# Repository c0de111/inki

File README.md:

# Tinta

Tinta is a battery-powered ePaper sign built around the Raspberry Pi Pico W. A real-time clock
wakes it on schedule, it fetches data over Wi-Fi, redraws the screen, and then switches itself off
completely in hardware — there is no sleep mode. A push button or an NFC tap wakes it on demand.
This approach earned an Honorable Mention in the "Least Power" category of
[Hackaday's 2026 Green-Powered Challenge](https://hackaday.com/2026/05/07/congratulations-to-the-green-powered-challenge-winners/).
One set of ordinary alkaline cells lasts thousands of refresh cycles, and the ePaper keeps its
image while the device is off.

This repository holds everything needed to build one: firmware, PCB design, 3D-printable enclosure,
and an optional telemetry service. Formerly published as **inki**.

[Crowd Supply campaign](https://www.crowdsupply.com/wake-electronics/tinta) · [Hackaday logs](https://hackaday.io/project/203726-tinta-low-power-wireless-epaper-device) · [Mastodon](https://hachyderm.io/@tinta) · [MakerTube](https://makertube.net/c/tinta) · [YouTube](https://www.youtube.com/@tinta-gadget)

<p align="center">
  
</p>

---

## Try it on a bare Pico W

No custom hardware required — the firmware runs on a stock Pico W with the display disabled.

1. Download a prebuilt UF2 from the [latest release](https://github.com/c0de111/tinta/releases/latest):
   [seatsurfing](https://github.com/c0de111/tinta/releases/latest/download/inki_seatsurfing.uf2) ·
   [historian](https://github.com/c0de111/tinta/releases/latest/download/inki_historian.uf2) ·
   [homematic](https://github.com/c0de111/tinta/releases/latest/download/inki_homematic.uf2)
2. Hold BOOTSEL while plugging in the Pico W, then copy the UF2 to the `RPI-RP2` drive.
3. The onboard LED blinks `inki` in Morse once it is up.
4. Connect to the Wi-Fi access point `inki-setup` and open `http://192.168.4.1`.

> Release artifacts and the setup access point still carry the old `inki` name.

## Build from source

Building, flashing, use-case selection, and the debug output are documented in
**[firmware/README.md](firmware/README.md)**. In short:

```
cd firmware/c
./build.sh --seatsurfing        # or --historian, --homematic, --weathermap
```

Requires the Pico SDK 2.1.0 (`PICO_SDK_PATH`), the ARM GNU toolchain, and CMake 3.12+.
The build produces a bootloader, two firmware slots for over-the-air updates, and a default
configuration image.

## Repository layout

```
firmware/       Pico W firmware in C — build system, use cases, drivers, web interface
hardware/       KiCad schematic and PCB (circuit/), FreeCAD and STL enclosure (enclosure/)
inki-monitor/   optional Python/Flask service collecting battery and Wi-Fi telemetry
scripts/        helper scripts
images/         photographs and diagrams used in the documentation
```

Each directory has its own README with the details.

## Hardware

The [enclosure](hardware/enclosure/) is modular and 3D-printable, with a dovetail mount: the
baseplate is glued or screwed to the wall and the sign clips on, so it lifts straight off for a
battery change.

The [circuit](hardware/circuit/) is a custom PCB carrying the Pico W, a real-time clock, MOSFET
power switching, battery monitoring, and an optional NFC front end.

## NFC

Boards with the optional ST25DV04KC tag can be reached by a phone **while the device is switched
off**: the phone's field powers the tag, the phone writes a short command into its EEPROM, and the
tag pulls the wake line. The Pico W then boots, reads the command over I²C, and acts on it — so a
tap can refresh the display or book a desk without the device having been powered at all.

The 16-byte wire format, the wake-source decision tree, and the antenna tuning helper are described
in [firmware/README.md](firmware/README.md) and [firmware/c/README.md](firmware/c/README.md). The
companion Android app lives in its own repository,
[wake-electronics/tinta-tap](https://github.com/wake-electronics/tinta-tap).

## Field results

A 4.2-inch unit running the Seatsurfing use case has been logged continuously in an office:

```
393 days, 5142 wake cycles on one set of three AAA cells
99.5 % day coverage; one outage in 393 days (66.6 h, external cause)
45-minute wake interval, median 2700.0 s over 13 months, no measurable drift
```

The 4.2-inch version is rated at about 5,000 wake cycles on three AAA cells, the 7.5-inch version
at about 10,000 on three AA cells. The unit above met that rating in the field and kept going.
Actual runtime follows the configured wake interval: a longer interval means fewer cycles per day
and a longer life on the same cells.

## License

This project contains both hardware and software components, licensed under separate terms:

- Everything in **/hardware** is licensed under the
  **CERN Open Hardware License v2 — Strongly Reciprocal (CERN-OHL-S-2.0)**.
- All original content in **/firmware** is licensed under the **Apache License, Version 2.0**.
  Bundled third-party components under `/firmware/c/third_party/` retain their upstream licenses —
  see [firmware/c/third_party/README.md](firmware/c/third_party/README.md).

See the LICENSE files in the respective directories for the full texts.

## Contributing

Issues and pull requests are welcome, particularly new use cases: one directory under
`firmware/c/` and one build flag, see [firmware/README.md](firmware/README.md).

Contact: [c0de@posteo.de](mailto:c0de@posteo.de)

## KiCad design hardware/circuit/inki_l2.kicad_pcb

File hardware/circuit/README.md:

# Tinta Circuit

This directory contains the schematic and hardware documentation for the **Tinta** PCB. There is also a former hand-solderable design, see [`legacy/`](legacy/).

---

## Overview

The Tinta circuit is designed for long-term operation (years) using 3×AAA or 3×AA
batteries. It uses a real-time clock for accurate timekeeping and wake-up scheduling —
either a DS3231 or RV-3028, detected automatically at runtime — combined with
MOSFET-based power switching to fully disconnect the controller between wake cycles.
During wake cycles, information is fetched via Wi-Fi and displayed on an ePaper display
that retains its content without power.

Key features:
- **MOSFET power switching** — Pico W fully disconnected during sleep, drawing only µA from the RTC and passives
- **Dual RTC support** — DS3231 or RV-3028, auto-detected at runtime via I2C
- **NFC wake and control** — ST25 chip powered by RF field when Pico is off
- **Board identity straps** — 4-bit hardware profile (GP0–GP3) selects display type and hardware variant at boot
- **Push button inputs** — manual wake, page selection, and on-demand fetches

---

## Concept, Functional Blocks and Components

The power control concept works as follows: in the default (sleep) state **Q1** is off
and the Pico W has no supply voltage. Three sources can wake the system: an RTC alarm
(DS3231 or RV-3028 via their INT pin), a **pushbutton**, or an NFC field event from the
ST25DV. Once Q1 switches on, the Pico pulls down the gate of **Q2**
to hold power, executes its program, sets the next RTC alarm, and cuts power by releasing
Q1 — returning to the µA idle state.

The ePaper display is controlled via SPI; RTC and NFC communicate via I2C.

Manual user interaction:
- **Pushbuttons #0–3**: on current boards the buttons are diode-OR'd into the wake line,
  so **any of the four wakes the device**. On earlier boards only #0 wakes it.
- **Pushbuttons #1–3**: also read once at startup to select the page — hold them while the
  device powers on. Page selection works the same on both board generations.
- **ST25 NFC**: write an NFC message to the tag to trigger a wake or page selection

<table>
<tr>
  <td style="padding: 20px;"></td>
  <td style="padding: 20px;"></td>
</tr>
<tr>
  <td align="center" style="padding: 20px;"><em>Tinta board – for details use KiCAD</em></td>
  <td align="center" style="padding: 20px;"><em>schematic – <a href="inki_l2.pdf">PDF</a> · for details use KiCAD</em></td>
</tr>
</table>

---

## Board Identity Straps (R8–R11)

Four 10k pull-up resistors on GP0–GP3 encode the board profile as a 4-bit code read at
boot to determine display type and hardware configuration.

- **Populated resistor** = bit reads `1`
- **Empty pad** = bit reads `0` (firmware applies internal pull-down)

| Code | R8  | R9  | R10 | R11 | Display | Coin Cell | Board                     |
|------|-----|-----|-----|-----|---------|-----------|---------------------------|
| 0x00 | —   | —   | —   | —   | ?       | yes       | Legacy / unstrapped       |
| 0x01 | 10k | —   | —   | —   | 7.5"    | yes       | L1, 7.5"                  |
| 0x02 | —   | 10k | —   | —   | 4.2"    | yes       | L1, 4.2"                  |
| 0x03 | 10k | 10k | —   | —   | 7.5"    | yes       | L2, 7.5"                  |
| 0x04 | —   | —   | 10k | —   | 4.2"    | yes       | L2, 4.2"                  |
| 0x05 | 10k | —   | 10k | —   | 7.5"    | no        | L2 minimal (no coin cell) |
| 0x06 | —   | 10k | 10k | —   | 4.2"    | no        | L2 minimal 4.2" (no coin cell) |
| 0x07–0x0F | — | — | — | — | —      | —         | (reserved)                |

I2C devices (RTC, NFC) are auto-detected via bus scan — not encoded in straps. Buttons
and LED do not require strap encoding.

---

## RTC Backend Selection

The firmware auto-detects the RTC at runtime via I2C bus scan:
- **DS3231** at 0x68 — classic, high-accuracy, moderate power (~200 µA active)
- **RV-3028** at 0x52 — ultra-low power (~45 nA idle), AMBA/Micro Crystal

Both provide alarm-based wake scheduling. The RV-3028 improves idle power budget
significantly for high-frequency refresh use cases.

---

## NFC Integration (ST25DV04KC)

The ST25DV NFC tag is powered from the RF field when the Pico is off (0 mA from battery).
Its GPIO-controlled VCC line (GP18) is held low during sleep. An NFC write from a phone
or reader pulls the ST25 INT line, which feeds into the wake circuit — waking the device
without a button press. The firmware reads the NFC payload at startup to determine the
requested page or action.

---

## Power Consumption and Estimations

Typical battery life can be estimated with
[`power_consumption_estimate.py`](power_consumption_estimate.py). Edit the parameters at the top
of the script and run it; the two examples below are its output.

### Power Consumption Estimate for 4.2"

Parameters taken from a real deployment — the field unit whose discharge curve is shown below.

**Used Parameters**

- **Idle current**: 5 µA (RTC consumption, residual current via pullups and others)
- **Activation consumption**: 0.250 mAh per wake-up (same for 4.2" and 7.5", measured — the
  ePaper refresh is not a significant contribution)
- **LED consumption** (included above): 0.021 mAh per wake-up
- **Wake-up schedule**: 18.3× per day, 5 days per week
- **Battery self-discharge**: 2.5 % per year
- **Battery capacity**: 1200 mAh (AAA batteries)

**Annualized Consumption Rates (approximate)**

- **Idle**: 43.8 mAh/year
- **Active (wake-ups)**: 1192.8 mAh/year

**⇒ Estimated battery lifetime: 350 days (≈ 0.96 years)**

**Yearly Breakdown**

| Year | Self-Discharge (mAh) | Fixed Consumption (mAh) |
|------|----------------------|--------------------------|
| 1    | 14.32                | 1185.75                  |

<p align="center">
  
</p>

<p align="center"><i>The same unit, measured: 393 days and 5142 wake cycles on one set of AAA
cells, logged at every wake. The scheduled interval held a median of exactly 2700.0 s, in each of
the 13 months, with a p95 jitter of about 7 s that did not change as the pack drained; the
discharge fits a straight line at R² = 0.987. One interruption occurred in the whole period,
66 hours in January 2026, appearing at the same time in the logs of five other units on the same
server.</i></p>

---

### Power Consumption Estimate for 7.5"

**Used Parameters**

- **Idle current**: 5 µA (RTC consumption, residual current via pullups and others)
- **Activation consumption**: 0.250 mAh per wake-up (same for 4.2" and 7.5", measured — the
  ePaper refresh is not a significant contribution)
- **LED consumption** (included above): 0.021 mAh per wake-up
- **Wake-up schedule**: 12× per day, 5 days per week
- **Battery self-discharge**: 2.5 % per year
- **Battery capacity**: 2500 mAh (AA batteries)

**Annualized Consumption Rates (approximate)**

- **Idle**: 43.8 mAh/year
- **Active (wake-ups)**: 782.1 mAh/year

**⇒ Estimated battery lifetime: 1065 days (≈ 2.92 years)**

**Yearly Breakdown**

| Year | Self-Discharge (mAh) | Fixed Consumption (mAh) |
|------|----------------------|--------------------------|
| 1    | 51.48                | 826.80                   |
| 2    | 29.82                | 826.80                   |
| 3    | 8.76                 | 757.20                   |

---

## RTC Backup Supply

Some boards carry a coin cell (**BT1**, e.g. CR1225) feeding the RTC's VBAT pin through a
diode-OR (**D1**, **D2**) alongside the main battery. It is optional and no longer fitted:
Tinta re-syncs the RTC from the network at every wake cycle, so the RTC only has to hold time
between cycles, which the main cells do. The board identity straps record which variant a given
board is.

---

## Key Components

- **Q1**: P-channel MOSFET — main power switch, disconnects Pico during sleep
- **Q2**: N-channel MOSFET — power latch (Pico holds itself on)
- **U1**: Raspberry Pi Pico W — main controller (Wi-Fi, ePaper, I2C, SPI)
- **U2**: DS3231SN or RV-3028 — RTC, alarm wake, I2C (auto-detected)
- **U3**: ST25DV04KC — NFC tag, ISO 15693, I2C, RF-powered when Pico off
- **R8–R11**: Board identity straps (10k pull-ups on GP0–GP3)
- **D1/D2, BT1**: optional diode-OR and coin cell for RTC backup (not fitted on current boards)

---

## Files

- `inki_l2.pdf` — schematic PDF (no KiCad required)
- `inki_l2.kicad_sch` — main schematic
- `inki_l2.kicad_pcb` — PCB layout
- `inki_l2_BOM.csv` — bill of materials
- `wake_sources.kicad_sch` — wake circuit sub-schematic
- `optional_i2c_device.kicad_sch` — optional I2C device sub-schematic
- `power_consumption_estimate.py` — battery lifetime model (edit parameters, run)
- `project-libraries/` — custom KiCad symbols and footprints

---

## Legacy Design

A former hand-solderable design is preserved in [`legacy/`](legacy/). It supports DS3231
only and has no NFC or identity straps, but can be assembled by an experienced solderer
without SMD equipment.

---

## License

This hardware is published under the **CERN-OHL-S v2** license.

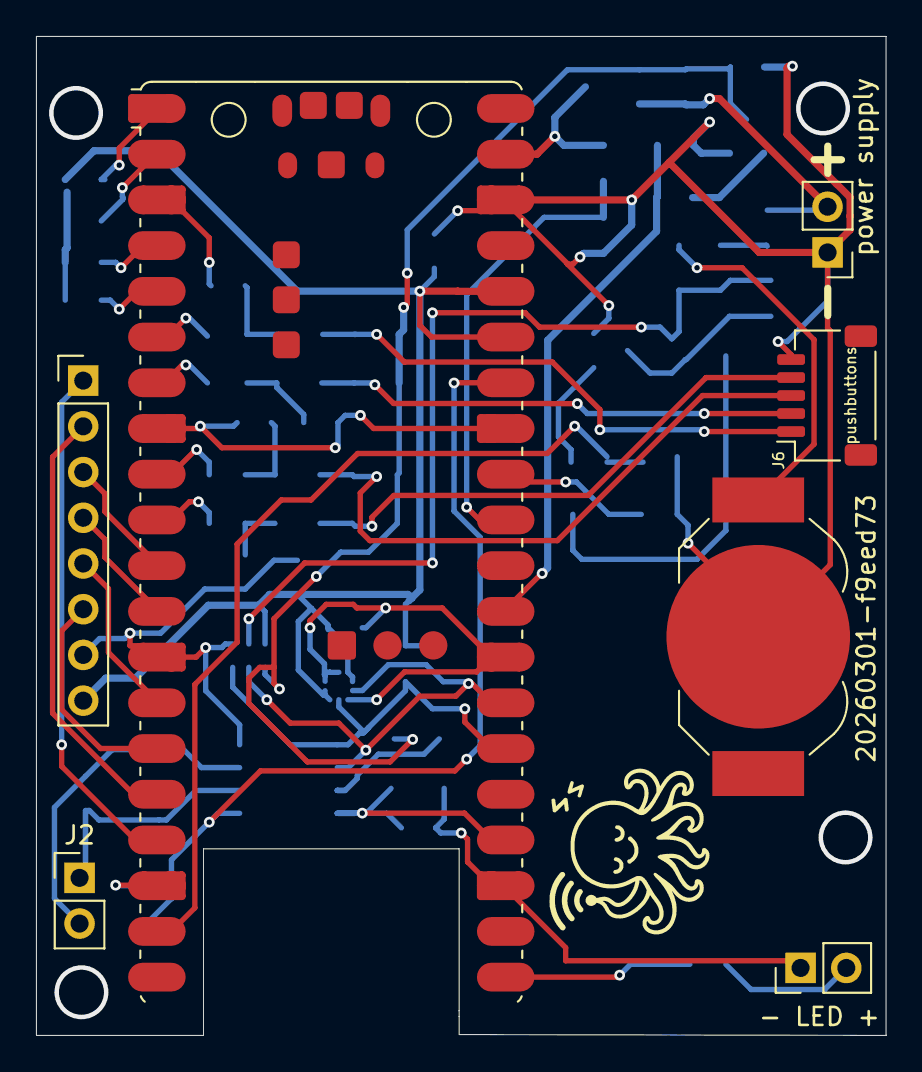
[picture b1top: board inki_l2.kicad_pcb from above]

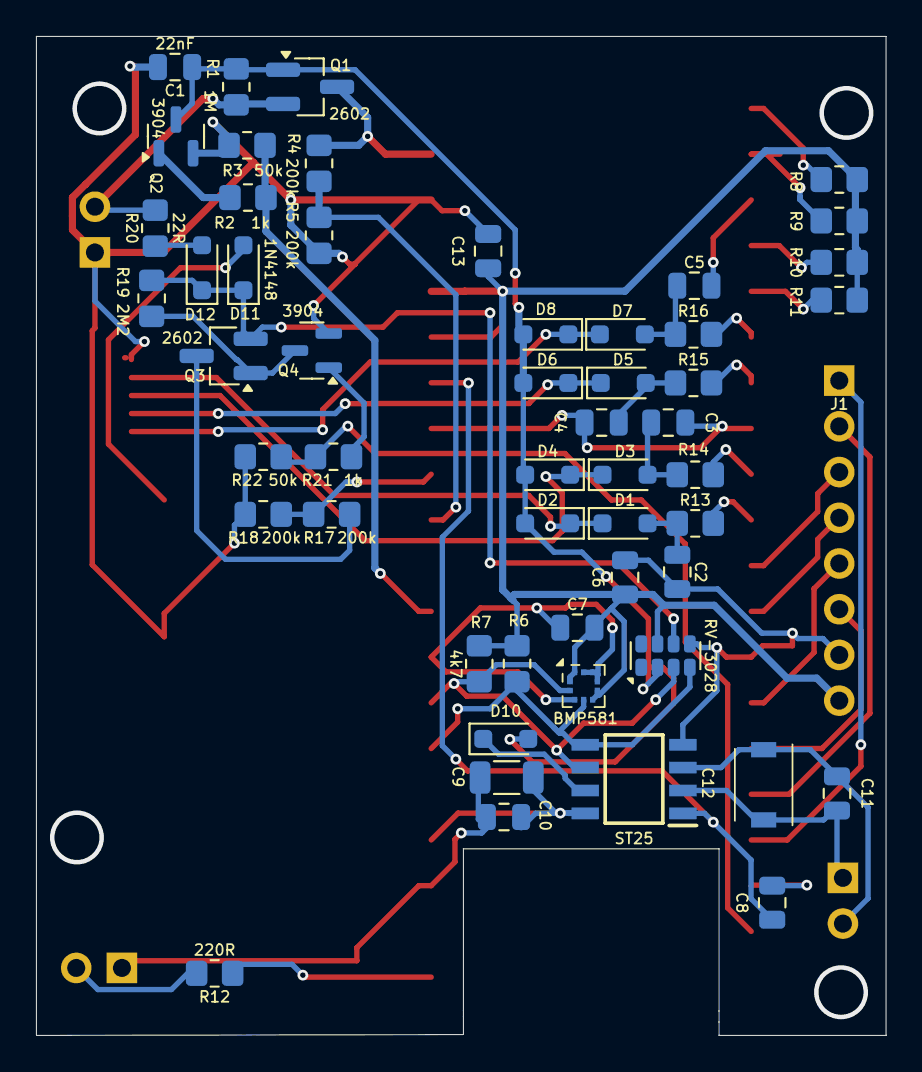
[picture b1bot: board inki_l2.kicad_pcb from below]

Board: 2 copper layers, 47.2 x 55.5 mm, 60 parts (53 on the bottom side), 47 nets.

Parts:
BT1: Coin Cell (RTC Backup); BatteryHolder_LINX_BAT-HLD-012-SMT
C1: 22nF; C_0805_2012Metric
C2, C3, C4, C5, C6, C7, C8, C10, C13: 100nF; C_0805_2012Metric
C9: 4.7uF; C_1206_3216Metric
C11: 10pF; C_0805_2012Metric
C12: JZ400
D1, D2, D3, D4, D5, D6, D7, D8, D10, D11: BAT54J; D_SOD-323_HandSoldering
D12: 1N4148; D_SOD-323_HandSoldering
J1: connector epaper; PinHeader_1x08_P2.54mm_Vertical
J2: antenna; PinHeader_1x02_P2.54mm_Vertical
J3: Battery 3xAA/AAA; PinHeader_1x02_P2.54mm_Vertical
J6: pushbuttons; JST_SH_SM05B-SRSS-TB_1x05-1MP_P1.00mm_Horizontal
J7: status LED; PinHeader_1x02_P2.54mm_Vertical
Q1, Q3: 2602; SOT-23_Handsoldering
Q2, Q4: 3904; SOT-23
R1: 1M; R_0805_2012Metric_Pad1.20x1.40mm_HandSolder
R2, R13, R14, R15, R16, R21: 1k; R_0805_2012Metric_Pad1.20x1.40mm_HandSolder
R3, R22: 50k; R_0805_2012Metric_Pad1.20x1.40mm_HandSolder
R4, R5, R17, R18: 200k; R_0805_2012Metric_Pad1.20x1.40mm_HandSolder
R6, R7: 4k7; R_0805_2012Metric_Pad1.20x1.40mm_HandSolder
R8, R9, R10, R11: 10k; R_0805_2012Metric_Pad1.20x1.40mm_HandSolder
R12: 220R; R_0805_2012Metric_Pad1.20x1.40mm_HandSolder
R19: 2M2; R_0805_2012Metric_Pad1.20x1.40mm_HandSolder
R20: 22R; R_0805_2012Metric_Pad1.20x1.40mm_HandSolder
U2: BMP581
U4: RV-3028; MicroCrystal_C7_SON-8_1.5x3.2mm_P0.9mm
U5: ST25; SOIC127P600X175-8N
pico1: SC0918; RaspberryPi_Pico_W_SMD

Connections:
3V3: C6.1, C7.1, C13.1, J1.8, R6.1, R7.1, R8.1, R9.1, R10.1, R11.1, U2.1 (VDDIO), U2.5 (SDO), U2.6 (CSB), U2.10 (VDD), U4.7 (VDD), pico1.35 (ADC_VREF), pico1.36 (3V3_OUT)
/BUSY: J1.1, pico1.17 (GP13)
/CLK: J1.5, pico1.14 (GP10)
/CS: J1.4, pico1.12 (GP9)
/DC: J1.3, pico1.11 (GP8)
/DIN: J1.6, pico1.15 (GP11)
/RST: J1.2, pico1.16 (GP12)
ADC_RTC_VBAT: R17.2, R18.1, pico1.32 (GP27)
BAT_RAW: J3.2, Q1.2 (S), R1.1, R20.2
GND: BT1.2 (-), C1.2, C2.2, C3.2, C4.2, C5.2, C6.2, C7.2, C8.2, C9.2, C10.2, C13.2, J1.7, J3.1, J6.5, J7.1, Q2.2 (E), Q4.2 (E), R3.2, R5.2, R18.2, R22.1, U2.3 (VSS), U2.7 (INT), U2.8 (VSS), U2.9 (VSS), U4.5 (VSS), U5.4 (VSS), pico1.3 (GND), pico1.8 (GND), pico1.13 (GND), pico1.18 (GND), pico1.23 (GND), pico1.28 (GND), pico1.33 (AGND), pico1.38 (GND)
unnamed: BT1.1 (+), D11.2 (A)
unnamed: C2.1, D1.2 (A), R13.1
unnamed: D1.1 (K), D2.1 (K), J6.4
unnamed: C3.1, D3.2 (A), R14.1
unnamed: D3.1 (K), D4.1 (K), J6.3
unnamed: C4.1, D5.2 (A), R15.1
unnamed: D5.1 (K), D6.1 (K), J6.2
unnamed: C5.1, D7.2 (A), R16.1
unnamed: D7.1 (K), D8.1 (K), J6.1
unnamed: D10.1 (K), U5.7 (GPO_(OPEN_DRAIN))
unnamed: D12.2 (A), R20.1
unnamed: C11.2, C12.2, J2.1, U5.2 (AC0)
unnamed: C11.1, C12.1, J2.2, U5.3 (AC1)
unnamed: J7.2, R12.2
unnamed: Q1.3 (D), R4.2, pico1.39 (VSYS)
unnamed: Q2.1 (B), R2.1
unnamed: Q3.3 (D), R17.1
unnamed: Q3.1 (G), Q4.3 (C), R19.2
unnamed: Q4.1 (B), R21.2
unnamed: R8.2, pico1.1 (GP0)
unnamed: R9.2, pico1.2 (GP1)
unnamed: R10.2, pico1.4 (GP2)
unnamed: R11.2, pico1.5 (GP3)
unnamed: R21.1, R22.2, pico1.19 (GP14)
unnamed: R12.1, pico1.21 (GP16)
unnamed: R2.2, R3.1, pico1.29 (GP22)
unnamed: R4.1, R5.1, pico1.31 (GP26)
PB1_GPIO: R13.2, pico1.10 (GP7)
PB2_GPIO: R14.2, pico1.9 (GP6)
PB3_GPIO: R15.2, pico1.7 (GP5)
PB4_GPIO: R16.2, pico1.6 (GP4)
RTC_VBAT: D11.1 (K), D12.1 (K), Q3.2 (S), R19.1, U4.6 (VBACKUP)
SCL: R7.2, U2.2 (SCK), U4.3 (SCL), U5.6 (SCL), pico1.27 (GP21)
SDA: R6.2, U2.4 (SDI), U4.4 (SDA), U5.5 (SDA), pico1.26 (GP20)
VCC_ST25: C9.1, C10.1, U5.8 (VCC), pico1.24 (GP18)
V_EH_ST25: C8.1, U5.1 (V_EH), pico1.34 (GP28)
WAKE: C1.1, D2.2 (A), D4.2 (A), D6.2 (A), D8.2 (A), D10.2 (A), Q1.1 (G), Q2.3 (C), R1.2, U4.2 (~INT)

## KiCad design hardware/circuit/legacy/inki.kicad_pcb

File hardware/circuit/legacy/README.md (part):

# inki Circuit

This repository contains the electronic schematic and hardware documentation for the **inki** project — a battery-powered, low-power circuit employing  a Raspberry Pi Pico W and a DS3231 RTC module for wireless ePaper display - as for instance for room signage.

---

## Overview
The inki circuit is designed for long-term operation (years) using 3×AAA or 3×AA batteries. It uses a DS3231 real-time clock for accurate timekeeping and wake-up scheduling, combined with MOSFET-based power switching to fully disconnect the controller to minimize power consumption between wake cycles. During wake cycles information is fetched via WIFI and displayed on an epaper which retains its display without power consumption.

---

## Concept, Functional Blocks and Components

In the default state of the circuit, **Q1** is in the off-state and the Pico does not get any supply voltage. Two events can switch **Q1** on via its gate and thus power the Pico: An alarm from the RTC **DS3231** via its INT pin, or a manual trigger via **pushbutton #0**. If this happens, the Pico will start, and as a first action in its program pull down the gate from **Q2**, so that power is maintained even if the push button is released by the user. The Pico will then execute its programme and always finish the programme with setting the next alarm in the **DS3231**, and, subsequently, finally cutting itself off power by switching **Q1** off. This leaves the Pico completely unpowered and the circuit back to the default state. In the default state, the circuits draws a **few µA** only, compared to **several mA** in the usual sleep modes of the Pico. During the wake cycle, the current drawn is approximately 50 mA for about 15 seconds. The epaper is controlled via SPI, the DS3231 via I2C.

<table>
<tr>
  <td style="padding: 20px;"></td>
  <td style="padding: 20px;"></td>
</tr>
<tr>
  <td align="center" style="padding: 20px;"><em>inki board – for details use KiCAD</em></td>
  <td align="center" style="padding: 20px;"><em>schematic – for details use KiCAD</em></td>
</tr>
</table>

Manual user interaction via:

- **SW1 / DIP switch**: Allow static configuration.
	-  **"gate"**: **pushbutton #0** can be connected to gate for manual triggering
	- **"always on"**: gate of **Q1** can be permanently grounded (powering Vsys of the Pico with Vcc) for debugging
	- **"LED"**: activate status LED, signaling running Pico
	- **"Vbat"**: Connect DS3231 Vbat to Vcc via **D2** (see below)

- **Pushbuttons** (**J2**, **J4**, **J5**):
	- **pushbutton #0** / **J2**: the same line as INT# and used for manual wake-up.
	- **pushbutton #1-3**: for manual user input, debounced by 1k resistors and 100nF caps, read once at start-up by the Pico -> First push **pushbutton #1-3**, only after that start Pico by **pushbutton #0**

---

## Power Consumption and Estimations

Typical battery life can be estimated with [`power_consumption_estimate.py`](../power_consumption_estimate.py) in the parent directory, example output for the 4.2" version:

### Power Consumption Estimate for 4.2"

**Used Parameters**

- **Idle current**: 5 µA (RTC consumption, residual current via pullups and others)
- **Activation consumption**: 0.250 mAh per wake-up (same for 4.2″ and 7.5″ versions, measured)
- **LED consumption** (included above): 0.021 mAh per wake-up
- **Wake-up schedule**: 7× per day, 5 days per week
- **Battery self-discharge**: 2.5 % per year
- **Battery capacity**: 1200 mAh (AAA batteries)

**Annualized Consumption Rates (approximate)**

- **Idle**: 43.8 mAh/year
- **Active (wake-ups)**: 456.2 mAh/year

**⇒ Estimated battery lifetime: 850 days (≈ 2.33 years)**

**Yearly Breakdown**

| Year | Self-Discharge (mAh) | Fixed Consumption (mAh) |
|------|----------------------|--------------------------|
| 1    | 23.43                | 500.55                   |
| 2    | 10.50                | 500.55                   |
| 3    | 0.68                 | 164.90                   |

This is based on measurements and gives estimations useful to gauge wake-up energy relative to idle current in order to optimize runtime versus refresh cycle.

---
### Power Consumption Estimate for 7.5"

**Used Parameters**

- **Idle current**: 5 µA (RTC consumption, residual current via pullups and others)
- **Activation consumption**: 0.250 mAh per wake-up (same for 4.2″ and 7.5″ versions, measured)
- **LED consumption** (included above): 0.021 mAh per wake-up
- **Wake-up schedule**: 48× per day, 7 days per week
- **Battery self-discharge**: 2.5 % per year
- **Battery capacity**: 2500 mAh (AA batteries)

**Annualized Consumption Rates (approximate)**

- **Idle**: 43.8 mAh/year
- **Active (wake-ups)**: 4380 mAh/year

**⇒ Estimated battery lifetime: 205 days (≈ 0.56 years)**

**Yearly Breakdown**

| Year | Self-Discharge (mAh) | Fixed Consumption (mAh) |
|------|----------------------|--------------------------|
| 1    | 17.58                | 2484.6                   |

This chart shows the measured energy consumption of the 7.5" prototype.

This is based on measurements and gives estimations useful to gauge wake-up energy relative to idle current in order to optimize runtime versus refresh cycle.

---

## Diode circuit for Vbat Supply for the DS3231

The goal of this circuit (**D1** and **D2**) is to supply the DS3231 real-time clock module with power at all times—either from the main power source (e.g. 3×AA(A) batteries) or, if unavailable, from a coin cell (e.g. CR1225). The switch between sources is passive, using one diode per supply path, and aims to minimize energy loss and especially protect the coin cell from unnecessary drain.

---

### Functional Principle

The two power sources (AAA and coin cell) are each connected to the VBAT pin through a diode. The diode with the higher input voltage (minus its forward voltage drop) determines which source supplies VBAT. The other diode remains reverse-biased and blocks current.

The intention is for the coin cell to only take over once the main battery voltage is no longer sufficient—ideally right before the microcontroller stops functioning due to low voltage. The DS3231 operates correctly on VBAT voltages between 2.3 V and 6.0 V, with 3.0 V being typical for coin-cell powered backup operation.

---

### D1 = 1N4148 (standard silicon diode), D2 = BAT54 (Schottky)

| Source      | Diode   | Forward Voltage (Vf) | Notes                                        |
|-------------|---------|----------------------|-----------------------------------------------|
| AAA         | 1N4148  | ~0.7 V               | Higher voltage drop, prioritizes AAA clearly |
| Coin cell   | BAT54   | ~0.2–0.3 V           | Low drop, ideal for backup                   |

#### Advantages
- **Clear prioritization**: Coin cell only activates when AAA voltage drops below ~3.8 V.
- **Coin cell is protected** for most of the battery life.
- **Simple component selection**, widely available parts.

#### Disadvantages
- At low AAA voltages (e.g. <3.3 V), VBAT may drop below 2.6 V.
- The 1N4148 causes a non-negligible drop in VBAT during AAA operation.

#### Measurement confirming the switch behavior

An oscilloscope measurement verifies the expected behavior:

Initially (high AAA voltage), VBAT closely follows the AAA level. As the AAA voltage drops and the output of the 1N4148 falls below the coin cell’s level minus the BAT54 drop, the coin cell takes over. VBAT then stabilizes around 3.1 V and becomes independent of AAA voltage.

---

### Self-Adjusting Coin Cell Protection

As the coin cell slowly discharges over time, its output voltage decreases (e.g. from 3.3 V to 2.8 V). This naturally delays its takeover, further prioritizing the AAA battery as long as possible. This behavior provides passive and automatic coin cell protection without requiring additional logic.

#### Reverse Leakage Behavior During Passive Source Switching

During normal operation, when one source (AAA or coin cell) supplies VBAT, the unused source’s diode is reverse-biased. This raises the question of whether significant leakage current could flow back into the inactive battery, potentially causing unnecessary drain over time.

At typical room temperatures (25 °C), the expected reverse leakage currents are extremely low:

| Diode         | Typical Reverse Current @ 25 °C, ~4 V | Notes |
|---------------|----------------------------------------|-------|
| 1N4148WS      | ~1–10 nA                              | Negligible |
| BAT54 (Schottky) | ~10–100 nA                          | Higher than silicon but still negligible |

Even under worst-case assumptions (maximum datasheet values at 20–25 V reverse voltage), the leakage remains in the nanoampere range. In real-world operation at ~3–4 V reverse voltage, the leakage current is orders of magnitude smaller than the typical standby current of the DS3231 RTC itself (1.5–2.0 µA).

Thus, no practical impact on battery life is expected from reverse leakage through either diode path. The diodes reliably block the inactive source without measurable drain, maintaining the energy-saving properties of the design.

---
## A few notes about some of the components

- **Q1**: TSM260P02CX, P-channel MOSFET — disconnects the Pico W from the battery supply during sleep. Controlled via DS3231 and push button #0.
- **D1**: BAT54 Schottky diode — supplies power from the battery pack to the circuit and DS3231 VCC.
- **D2**: BAT54 Schottky diode — connects the optional coin cell to DS3231 VBAT for backup operation.
- **R1–R3**: Gate resistors for Q1 — control gate behavior during transitions, including pull-up (R2) and pull-down (R3).
- **INT#/Button**: Wake-up signal sourced from either the DS3231 alarm output or a manual pushbutton connected in parallel. The gate of Q1 is pulled low through these paths, enabling the Pico's power.
- **R7, R8**: Voltage divider for measuring the 3×AAA battery voltage. Divider is only active when **Q1** is conducting (i.e., during Pico operation).
- **U2**: DS3231SN — provides accurate timekeeping, I²C communication, and a programmable alarm interrupt controlling the whole circuit.
- **J4**: Coin cell holder — supplies VBAT to DS3231 when main power is lost.
- The DS3231 remains powered at all times to maintain time and alarm functionality.
- **Q3**: IRLML6344 N-channel MOSFET — enables a separate divider (**R1** and **R14**) to measure the voltage of the RTC coin cell (Vbat). Controlled via GP14.
- **R15**: Pull-down on Q3 gate — ensures that Q3 remains off when unpowered to eliminate leakage current.
- **GP14**: GPIO enabling VBAT divider (Q3).
- **GP27**: Analog input (ADC) for measuring voltage from the divider.

## Files and Folders

- `esign.kicad_sch`: Main schematic
- `esign.kicad_pcb`: PCB layout
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
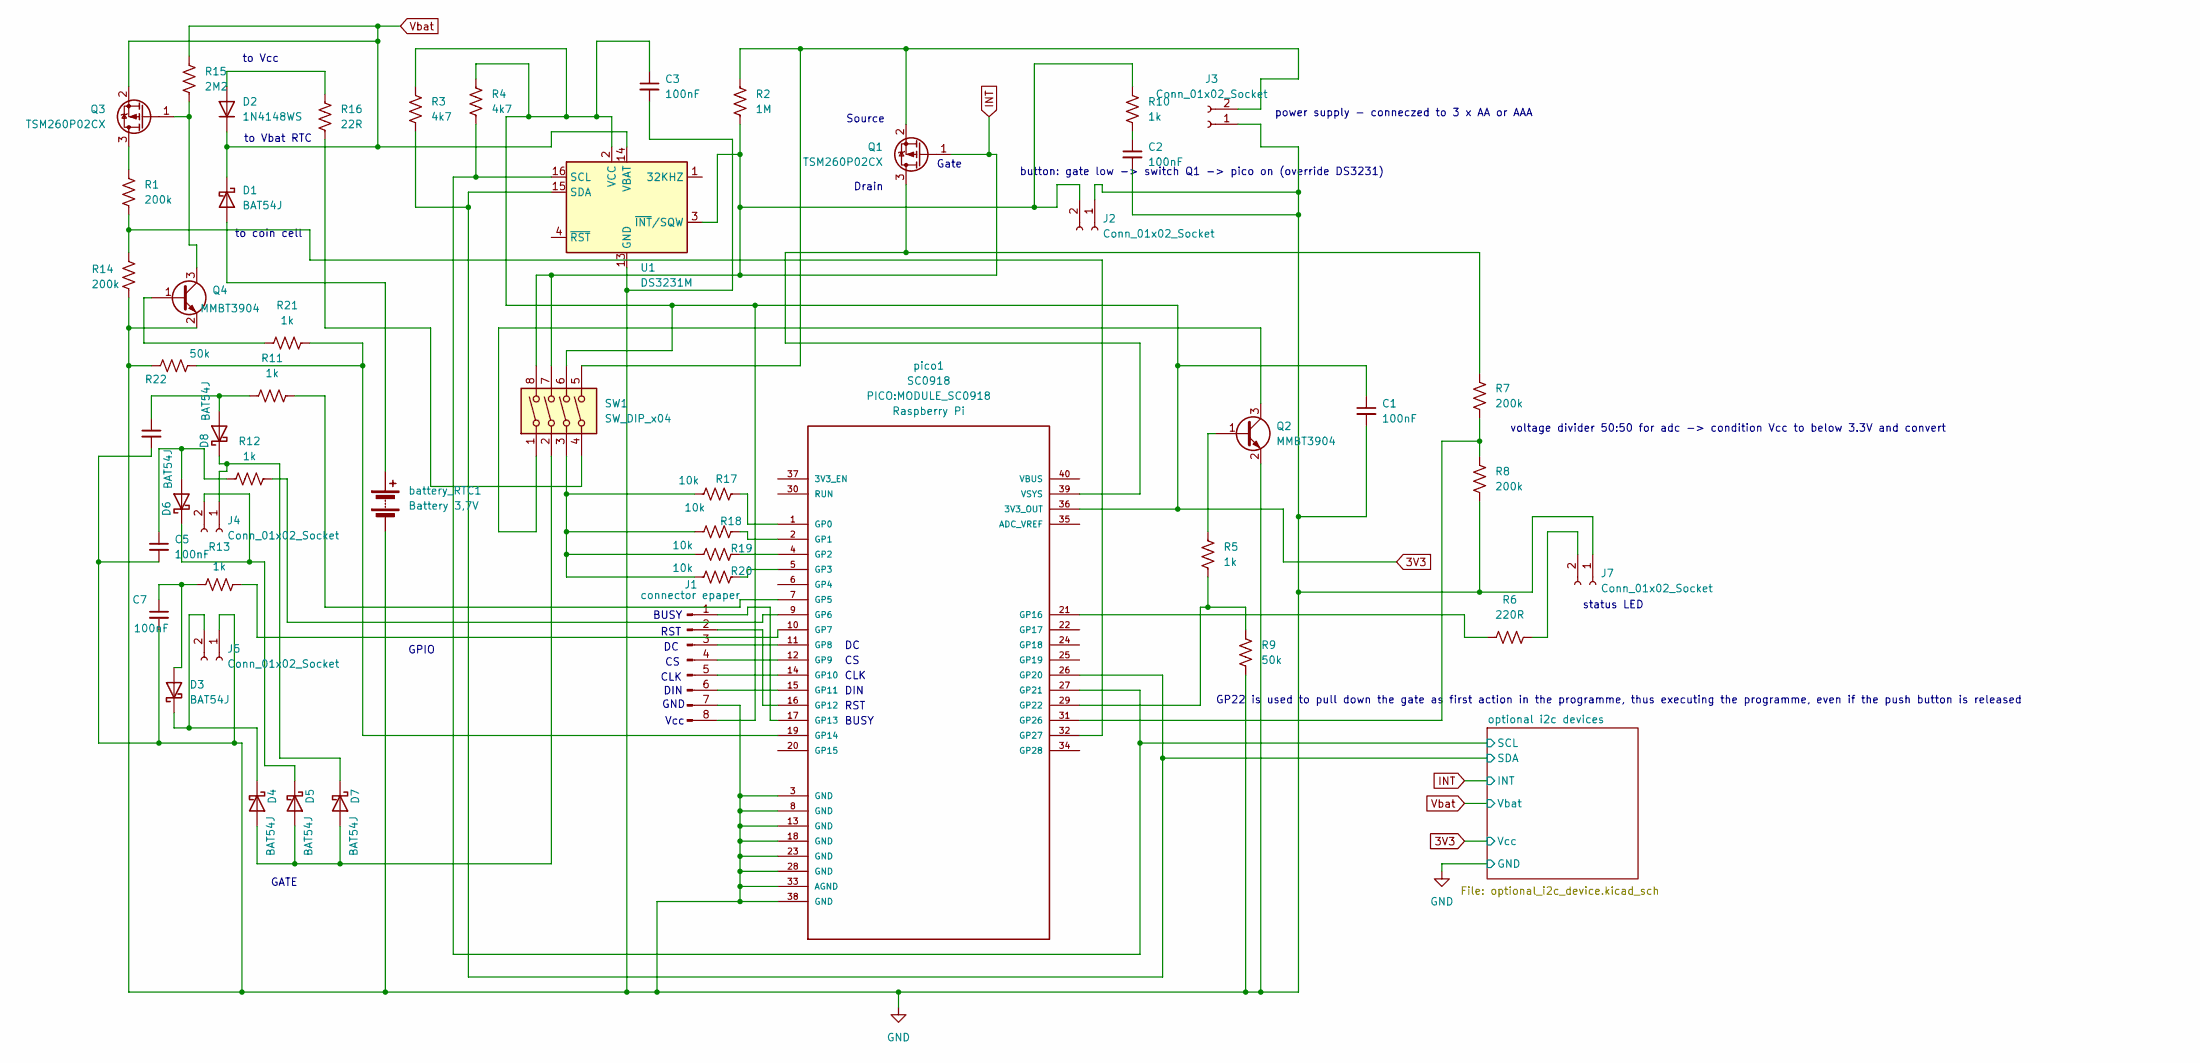
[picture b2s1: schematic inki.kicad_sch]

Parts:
C1, C2, C3, C4, C5, C7: 100nF; C_0805_2012Metric
D1, D3, D4, D5, D6, D7, D8: BAT54J; D_SOD-323_HandSoldering
D2: 1N4148WS; D_SOD-323_HandSoldering
J1: connector epaper; PinHeader_1x08_P2.54mm_Vertical
J2, J3, J4, J5, J7: Conn_01x02_Socket; PinHeader_1x02_P2.54mm_Vertical
Q1, Q3: TSM260P02CX; SOT-23_Handsoldering
Q2, Q4: MMBT3904; SOT-23
R1, R7, R8, R14: 200k; R_0805_2012Metric_Pad1.20x1.40mm_HandSolder
R2: 1M; R_0805_2012Metric_Pad1.20x1.40mm_HandSolder
R3, R4: 4k7; R_0805_2012Metric_Pad1.20x1.40mm_HandSolder
R5, R10, R11, R12, R13, R21: 1k; R_0805_2012Metric_Pad1.20x1.40mm_HandSolder
R6: 220R; R_0805_2012Metric_Pad1.20x1.40mm_HandSolder
R9, R22: 50k; R_0805_2012Metric_Pad1.20x1.40mm_HandSolder
R15: 2M2; R_0805_2012Metric_Pad1.20x1.40mm_HandSolder
R16: 22R; R_0805_2012Metric_Pad1.20x1.40mm_HandSolder
R17, R18, R19, R20: 10k; R_0805_2012Metric_Pad1.20x1.40mm_HandSolder
SW1: SW_DIP_x04; SW_DIP_SPSTx04_Slide_9.78x12.34mm_W8.61mm_P2.54mm
U1: DS3231M; SOIC-16W_7.5x10.3mm_P1.27mm
battery_RTC1: Battery 3,7V; BatteryHolder_LINX_BAT-HLD-012-SMT
pico1: SC0918; MODULE_SC0918; PARTREV 1.6

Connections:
3V3: C1.1, C3.1, J1.8, R3.1, R4.1, SW1.6, U1.2 (VCC), pico1.36 (3V3_OUT); also elsewhere on the board
/optional i2c devices/SCL: R4.2, U1.16 (SCL), pico1.27 (GP21); also elsewhere on the board
/optional i2c devices/SDA: R3.2, U1.15 (SDA), pico1.26 (GP20); also elsewhere on the board
GND: C1.2, C2.2, C3.2, C4.2, C5.2, C7.2, J1.7, J2.1, J3.1, J5.1, J7.1, Q2.2 (E), Q4.2 (E), R8.2, R9.2, R14.2, R22.1, U1.5 (GND), U1.6 (GND), U1.7 (GND), U1.8 (GND), U1.9 (GND), U1.10 (GND), U1.11 (GND), U1.12 (GND), U1.13 (GND), battery_RTC1.2 (-), pico1.3 (GND), pico1.8 (GND), pico1.13 (GND), pico1.18 (GND), pico1.23 (GND), pico1.28 (GND), pico1.33 (AGND), pico1.38 (GND); also elsewhere on the board
INT: J2.2, Q1.1 (G), R2.2, R10.2, SW1.7, SW1.8, U1.3 (~INT/SQW); also elsewhere on the board
unnamed: C2.1, R10.1
unnamed: D1.2 (A), battery_RTC1.1 (+)
unnamed: D2.2 (A), R16.1
unnamed: C7.1, D3.2 (A), R13.2
unnamed: D3.1 (K), D4.1 (K), J5.2
unnamed: D4.2 (A), D5.2 (A), D7.2 (A), SW1.2
unnamed: D5.1 (K), D6.1 (K), J4.2
unnamed: C5.1, D6.2 (A), R12.2
unnamed: D7.1 (K), D8.1 (K), J4.1
unnamed: C4.1, D8.2 (A), R11.2
unnamed: J1.1, pico1.17 (GP13)
unnamed: J1.2, pico1.16 (GP12)
unnamed: J1.3, pico1.11 (GP8)
unnamed: J1.4, pico1.12 (GP9)
unnamed: J1.5, pico1.14 (GP10)
unnamed: J1.6, pico1.15 (GP11)
unnamed: J3.2, Q1.2 (S), R2.1, SW1.5
unnamed: J7.2, R6.2
unnamed: Q1.3 (D), R7.1, pico1.39 (VSYS)
unnamed: Q2.1 (B), R5.1
unnamed: Q2.3 (C), SW1.1
unnamed: Q3.3 (D), R1.1
unnamed: Q3.1 (G), Q4.3 (C), R15.2
unnamed: Q4.1 (B), R21.2
unnamed: R16.2, SW1.4
unnamed: R17.1, R18.1, R19.1, R20.1, SW1.3
unnamed: R17.2, pico1.1 (GP0)
unnamed: R18.2, pico1.2 (GP1)
unnamed: R19.2, pico1.4 (GP2)
unnamed: R20.2, pico1.5 (GP3)
unnamed: R11.1, pico1.7 (GP5)
unnamed: R12.1, pico1.9 (GP6)
unnamed: R13.1, pico1.10 (GP7)
unnamed: R21.1, R22.2, pico1.19 (GP14)
unnamed: R6.1, pico1.21 (GP16)
unnamed: R5.2, R9.1, pico1.29 (GP22)
unnamed: R7.2, R8.1, pico1.31 (GP26)
unnamed: R1.2, R14.1, pico1.32 (GP27)
Vbat: D1.1 (K), D2.1 (K), Q3.2 (S), R15.1, U1.14 (VBAT); also elsewhere on the board

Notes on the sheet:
CLK
Vcc
to Vcc
voltage divider 50:50 for adc -> condition Vcc to below 3.3V and convert
button: gate low -> switch Q1 -> pico on (override DS3231)
to Vbat RTC
status LED
RST
GP22 is used to pull down the gate as first action in the programme, thus executing the programme, even if the push button is released
DIN
GND
BUSY
Drain
GATE
Source
GPIO
to coin cell
power supply - conneczed to 3 x AA or AAA
Gate

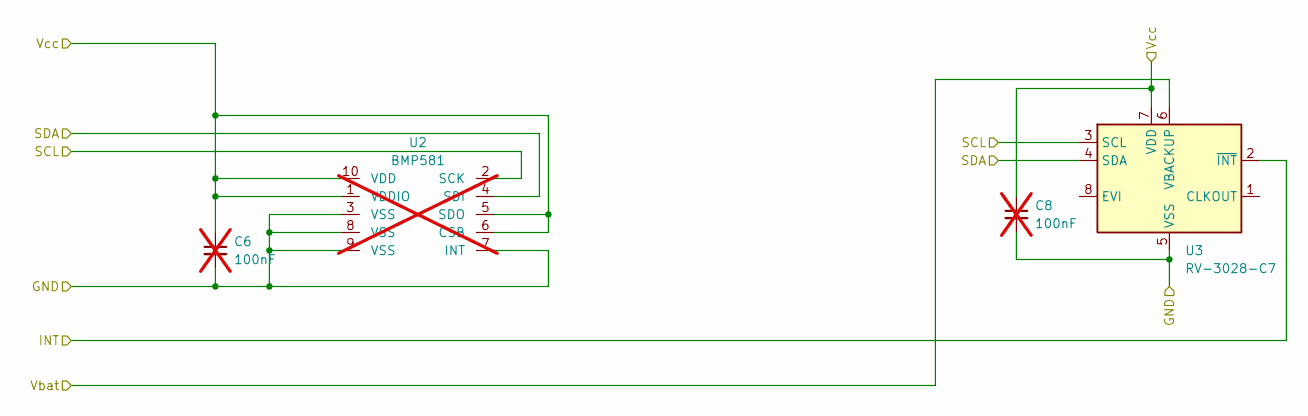
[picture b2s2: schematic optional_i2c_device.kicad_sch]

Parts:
C6, C8: 100nF; C_0805_2012Metric; not fitted
U2: BMP581; not fitted
U3: RV-3028-C7; MicroCrystal_C7_SON-8_1.5x3.2mm_P0.9mm

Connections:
3V3: C6.1, C8.1, U2.1 (VDDIO), U2.5 (SDO), U2.6 (CSB), U2.10 (VDD), U3.7 (VDD); also elsewhere on the board
/optional i2c devices/SCL: U2.2 (SCK), U3.3 (SCL); also elsewhere on the board
/optional i2c devices/SDA: U2.4 (SDI), U3.4 (SDA); also elsewhere on the board
GND: C6.2, C8.2, U2.3 (VSS), U2.7 (INT), U2.8 (VSS), U2.9 (VSS), U3.5 (VSS); also elsewhere on the board
INT: U3.2 (~INT); also elsewhere on the board
Vbat: U3.6 (VBACKUP); also elsewhere on the board

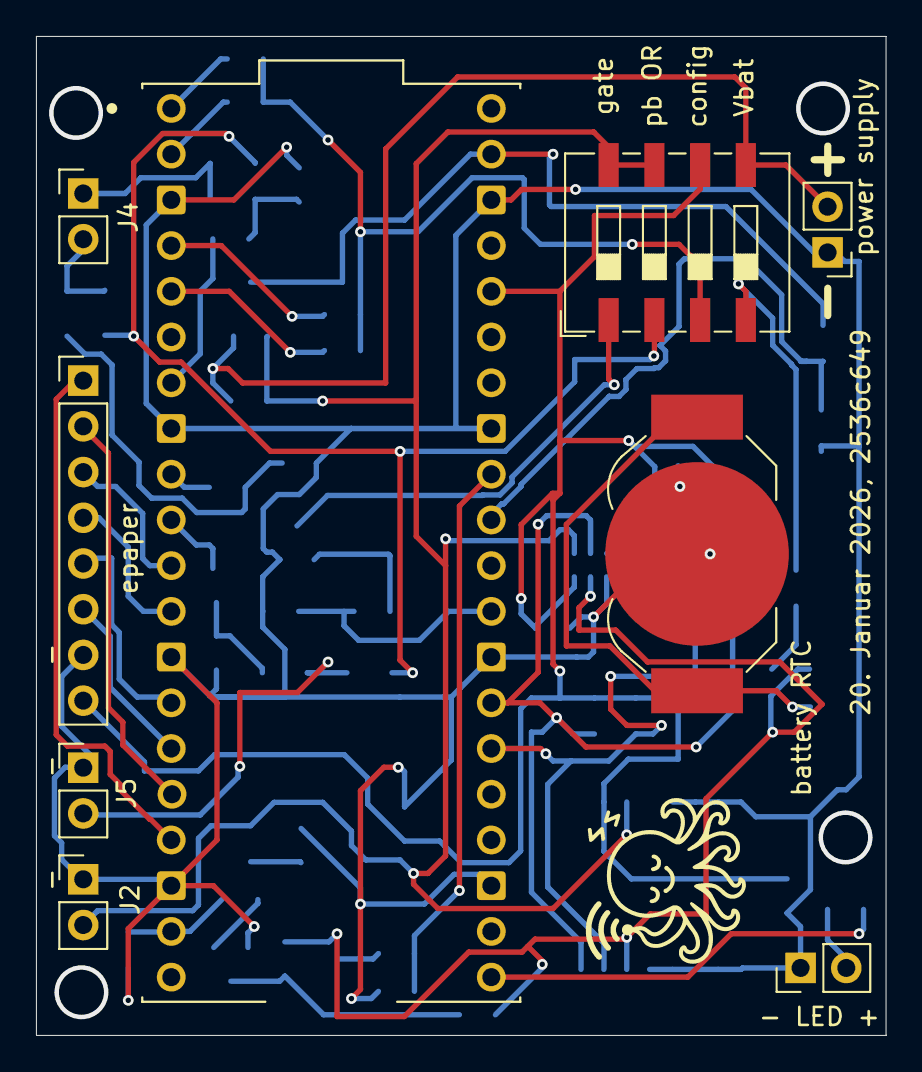
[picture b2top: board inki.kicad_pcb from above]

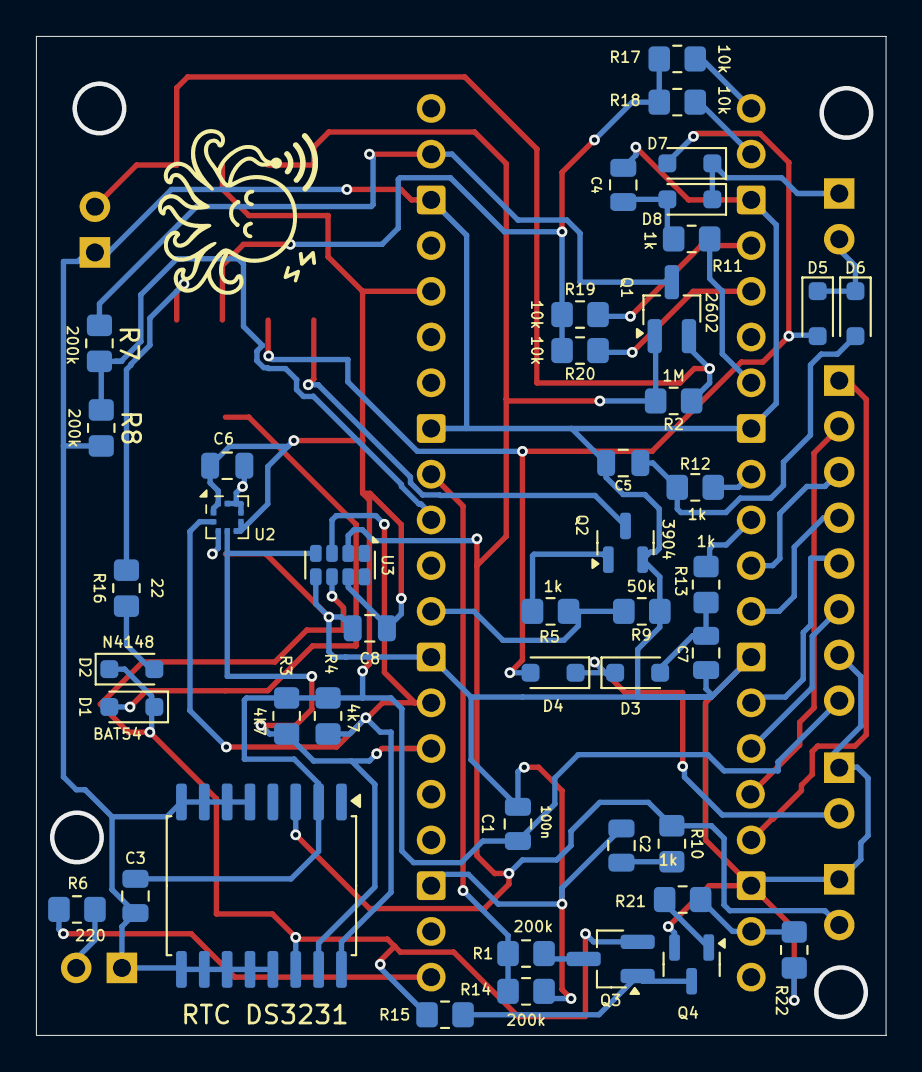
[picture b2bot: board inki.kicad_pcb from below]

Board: 2 copper layers, 47.2 x 55.5 mm, 54 parts (45 on the bottom side), 44 nets.

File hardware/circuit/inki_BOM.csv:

"Reference","Value","Datasheet","Footprint","Qty","DNP"
"battery_RTC1","Battery 3,7V","~","Battery:BatteryHolder_LINX_BAT-HLD-012-SMT","1",""
"C1,C2,C3,C4,C5,C6,C7","100nF","~","Capacitor_SMD:C_0805_2012Metric","7",""
"D1,D3,D4,D5,D6,D7,D8","BAT54J","https://assets.nexperia.com/documents/data-sheet/BAT54J.pdf","Diode_SMD:D_SOD-323_HandSoldering","7",""
"D2","1N4148WS","https://www.vishay.com/docs/85751/1n4148ws.pdf","Diode_SMD:D_SOD-323_HandSoldering","1",""
"J1","connector epaper","~","Connector_PinHeader_2.54mm:PinHeader_1x08_P2.54mm_Vertical","1",""
"J2,J3,J4,J5,J7","Conn_01x02_Socket","~","Connector_PinHeader_2.54mm:PinHeader_1x02_P2.54mm_Vertical","5",""
"pico1","SC0918","https://datasheets.raspberrypi.com/picow/pico-w-datasheet.pdf","PICO:MODULE_SC0918","1",""
"Q1,Q3","TSM260P02CX","https://www.taiwansemi.com/products/datasheet/TSM2301A_C15.pdf","Package_TO_SOT_SMD:SOT-23_Handsoldering","2",""
"Q2,Q4","MMBT3904","https://www.onsemi.com/pdf/datasheet/pzt3904-d.pdf","Package_TO_SOT_SMD:SOT-23","2",""
"R1,R7,R8,R14","200k","~","Resistor_SMD:R_0805_2012Metric_Pad1.20x1.40mm_HandSolder","4",""
"R2","1M","~","Resistor_SMD:R_0805_2012Metric_Pad1.20x1.40mm_HandSolder","1",""
"R3,R4","4k7","~","Resistor_SMD:R_0805_2012Metric_Pad1.20x1.40mm_HandSolder","2",""
"R5,R10,R11,R12,R13,R21","1k","~","Resistor_SMD:R_0805_2012Metric_Pad1.20x1.40mm_HandSolder","6",""
"R6","220R","~","Resistor_SMD:R_0805_2012Metric_Pad1.20x1.40mm_HandSolder","1",""
"R9,R22","50k","~","Resistor_SMD:R_0805_2012Metric_Pad1.20x1.40mm_HandSolder","2",""
"R15","2M2","~","Resistor_SMD:R_0805_2012Metric_Pad1.20x1.40mm_HandSolder","1",""
"R16","22R","~","Resistor_SMD:R_0805_2012Metric_Pad1.20x1.40mm_HandSolder","1",""
"R17,R18,R19,R20","10k","~","Resistor_SMD:R_0805_2012Metric_Pad1.20x1.40mm_HandSolder","4",""
"SW1","SW_DIP_x04","~","Button_Switch_SMD:SW_DIP_SPSTx04_Slide_9.78x12.34mm_W8.61mm_P2.54mm","1",""
"U1","DS3231M","http://datasheets.maximintegrated.com/en/ds/DS3231.pdf","Package_SO:SOIC-16W_7.5x10.3mm_P1.27mm","1",""
"U2","BMP581","","inki:BMP581","1",""

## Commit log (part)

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2025-04-06 edit README.md
2025-04-06 license, folders added
2025-04-06 initial commit case files 4_2
2025-04-08 added video for case illustration
2025-04-10 work on README.md
2025-04-10 work on README.md, videos
2025-04-11 small edits
2025-05-11 update docs
2025-05-11 update docs circuit
2025-05-12 edited gif
2025-06-08 edit docs
2025-06-08 firmware with seatsurfing availability endpoint
2025-06-08 docs edited
2025-06-08 edits to docs
2025-06-08 small video of esign in action
2025-06-08 added docs
2025-08-02 KiCAD schematics and board
2025-08-03 rebuild firmware: bootloader, flash, web interface
2025-08-03 edits README
2025-08-03 cleaned up build and README
2025-08-03 README edits, more images
2025-08-03 added screenshots for README
2025-08-05 clean-up
2025-08-05 minor edits
2025-08-22 refactor: extract utility functions from webserver.c
    Extract three utility functions to new webserver_utils module:
    - url_decode(): URL decoding functionality
    - crc32_calculate(): CRC32 calculation with firmware validation
    - safe_flash_copy(): Safe flash memory copy operations
2025-08-23 edit .gitignore
2025-08-24 refactor: extract HTML page functions to webserver_pages.c
2025-08-24 refactor: move form handlers to webserver_pages.c
2025-08-24 refactor: complete route table implementation, replace if-else chains
2025-08-24 refactor: clean up recv_cb routing logic, preserve chunked transfers
2025-08-24 refactor: optimize recv_cb structure, readability and eliminate duplication
2025-08-24 refactor: reorganize webserver functions into utility and flash modules
2025-08-24 style: improve code formatting, comments, and naming
2025-08-24 docs: improve webserver_pages structure and documentation
2025-08-24 fix: correct upload_session variable declaration for proper module access
2025-08-25 fix: move flash functions back to webserver.c to fix firmware update
2025-08-25 refactor: consolidate base64 encoding into dedicated module
2025-08-25 refactor: move HTTP auth header creation to base64 module
2025-08-25 add: UF2 creation script and base64 documentation
2025-08-27 refactor: replace basic HTTP client with chunked transfer architecture
2025-08-28 combined historian and seatsurfing, very rough at this stage
2025-08-28 refactor: unify communication functions and eliminate code duplication
2025-08-28 refactor: consolidate includes and remove duplicates
2025-08-28 refactor: implement unified callback architecture for all use cases
2025-08-28 refactor: remove legacy buffer code and add documentation for adding additional use cases
2025-08-28 add: build-time use case selection
2025-08-28 update: README with build options and use case selection
2025-08-28 cleaned-up http_client.c
2025-08-29 historian implementation: ifdefs, flash
2025-08-29 fix: align historian config structure with actual runtime usage
2025-08-29 fix: harden recv handling, dynamic fallback body, non-2xx as error
2025-08-29 fix: harden recv loop, dynamic fallback body, status handling, and cleanup on tcp errors
2025-08-29 update: clarify http/1.0 (no chunked) and centralize HTTP buffer sizes
2025-08-29 fix: use size_t for size math and add overflow checks in Content-Length and fallback paths
2025-08-29 centralize wifi_connect in wifi.c; remove duplicate from http_client.c
2025-08-29 refactor: extract historian utils (time, JSON, request build) to historian_client and include in build
2025-08-29 refactor: extract seatsurfing request builder to seatsurfing_client; keep orchestration in http_client for parity with historian
2025-08-30 add: emergency mode without ePaper (EPAPER_NONE) — boot into Wi‑Fi setup; fallback on ePaper init failure; default epaper=none
2025-08-30 add: LED status indicators (ext GP16 + Pico W) with config switches; non-blocking Morse “inki” during Wi‑Fi setup
2025-08-30 add: web route “Morse Your Message” with non-blocking LED morse engine; support custom speed and stop control via POST form
2025-08-31 update: replace /morse with unified /message page (Morse on LED or ePaper print)
2025-08-31 add: vendor cJSON under third_party/cjson and update build paths
2025-08-31 info for cJSON repo
2025-08-31 chore: prepare cJSON subtree import (remove manual vendor)
2025-08-31 Squashed 'third_party/cjson/' content from commit acc7623
    git-subtree-dir: third_party/cjson
    git-subtree-split: acc76239bee01d8e9c858ae2cab296704e52d916
2025-08-31 chore: remove cJSON subtree at repo root
2025-08-31 Squashed 'firmware/c/third_party/cjson/' content from commit acc7623
    git-subtree-dir: firmware/c/third_party/cjson
    git-subtree-split: acc76239bee01d8e9c858ae2cab296704e52d916
2025-08-31 docs: add quick cJSON update check and commands to UPSTREAM.md
2025-08-31 chore: remove manual ds3231 vendor (prepare subtree import)
2025-08-31 Squashed 'firmware/c/third_party/ds3231/' content from commit ea1d438
    git-subtree-dir: firmware/c/third_party/ds3231
    git-subtree-split: ea1d4388991cfe892c4ce7ab6ca847bf5fc592e7
2025-08-31 upstream info ds3231
2025-09-01 add: RP2040 on-chip temperature read and Device Status display
2025-09-01 add: DS3231 temperature read and Device Status display
2025-09-01 add: log Wi‑Fi RSSI after successful STA connect
2025-09-01 add: docs on Pico W cores and Wi‑Fi background arch
2025-09-01 add: Device Status memory info (heap used/headroom, stack margin)
2025-09-01 add: Device Status ASCII memory map and addresses
2025-09-01 add: historian: start web interface when page 4 is pressed
2025-09-01 update: format RTC temp to 0.25°C steps; log RSSI before Wi‑Fi off
2025-09-01 update: added logo to historian page 0
2025-09-02 fix: generate one-file UF2 (bootloader+slot0+config) with valid_flag=1; name UF2 by use case; add guarded 2s USB wait in bootloader; make default_config build lean (guard ds3231/lwIP)
    - UF2: create monolithic BIN (0xFF-filled), place bootloader @0x0, slot0 (patched) @0x010000, config @0x1E7000; convert via Microsoft uf2conv to a single stream. Avoid multi-UF2 concatenation which c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
    - Slot validity: patch slot0 valid_flag=1 before UF2 so bootloader recognizes it on blank devices.
    - Bootloader: add #ifdef USB_BOOTLOADER_ENABLE guarded ~2s USB wait to allow log capture without blocking boot.
    - De
2025-09-02 update circuit: pullups for hardwired epaper config, status LED
2025-09-02 ci: add release workflow to build and attach UF2 artifacts on tags (historian + seatsurfing)
2025-09-02 docs: add Releases link and improve 'Try it' section for prebuilt UF2 quick start
2025-09-02 edit: tag on pcb
2025-09-03 ci: remove misplaced workflow directory under firmware/c
2025-09-05 direct links in README
2025-09-07 add: Homematic use case scaffolding (config + flash I/O + web UI + routing), build flag/UF2 suffix, and http_client Homematic branch stub
2025-09-08 fix(homematic): correct form field indexing, add full HTTP request logging, include .homematic_config in default UF2, and render page 0 values
2025-09-09 changed to sequential single queries for homematic
2025-09-09 feat(homematic): switch to sequential single-call engine with robust TCP close handoff; add per-item retry and headers; show partial results, fix(http): ignore stale PCB callbacks and post-success TC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
2025-09-11 edited debug messages
2025-09-11 - ui: adapt Device Config by use case (SeatSurfing keeps full Room Settings; Historian/Homematic show “Name & Title” only; seat‑limit JS only for SeatSurfing)
2025-09-11 add: Homematic units + boolean toggle UI
2025-09-12 add: Homematic UI polish, service footer, and robust parsing
2025-09-12 fix(homematic): stable parsing
2025-09-13 ui(homematic): compact form layout and column widths; rename label
2025-09-14 feat: add weathermap use case with HTTPS client and TLS 1.2 support
2025-09-15 refactor: reorganize fonts for hybrid subtree structure
    - Move Ubuntu Mono fonts to fonts_custom/ directory
    - Add UPSTREAM.md for GUI library documentation
    - Prepare for Waveshare subtree integration
    Following cJSON subtree pattern for better upstream management
2025-09-15 feat: 4 shades of gray support for ePaper display, tested on 4.2 version
2025-09-19 new use case weathermap, first part: fetching of geodata and display map in gray-scale on 4.2 epaper
2025-09-28 modified pcb (all smds to one side), weathermap work
2025-09-28 work on webpage, photos
2025-09-28 fixed image's path
2025-09-28 fixed paths for webpage
2025-09-28 fix: links webpage
2025-09-28 work on webpage
2025-09-28 updates webpage
2025-09-28 .gitignore update
2025-10-03 docs and webpage update
2025-10-19 update: replace fallback logos with inki logo and set use-case room names
2025-10-19 refactor: prepare generalized page routing with historian placeholders
2025-10-19 fix: revert lwIP tuning and avoid sleeps during firmware uploads
2025-10-19 update progress windows for firmware updates
2025-10-19 switch morse back on for webinterface
2025-10-19 fix: usb wait time removed
2025-10-19 fixed page layout historian
2025-10-19 feat: add homematic-specific page routing and placeholders
2025-10-19 fix: web interface call homematic
2025-10-21 silk screen updates
2025-10-21 edit pcb: add bmp581
2025-10-22 feat: weathermap fetch fallback rendering
2025-10-22 fix: seed weathermap defaults and render fallback page
2025-10-22 default config weathermap
2025-10-22 edits homematic page 0
2025-10-22 edits seatsurfing page 0
2025-10-22 pcb update: bmp581 sensor added
2025-11-16 hardware: gate VBAT divider with PFET to stop leakage in off-state
2025-11-29 improved coin cell voltage measurement
2026-01-17 updated pcb, unified part names, added BOM
2026-01-17 chore(deps-dev): bump uri from 1.0.3 to 1.0.4 in /docs
    Bumps [uri](https://github.com/ruby/uri) from 1.0.3 to 1.0.4.
    - [Release notes](https://github.com/ruby/uri/releases)
    - [Commits](https://github.com/ruby/uri/compare/v1.0.3...v1.0.4)
    ---
    updated-dependencies:
    - dependency-name: uri
2026-01-17 add optional i2c sensor sheet and align bom values
2026-01-20 added optional i2c device, added gerber files - not tested! Use with care!
2026-01-20 pcb edit - silk screen
2026-01-22 Publish route
2026-01-22 edits README.md
2026-01-22 edits
2026-01-22 added ignore files to publish-allowlist
2026-01-23 fix: patch pico-sdk pioasm for gcc15, SDK bump TODO
2026-01-24 prep seatsurfing multi-seat config and switch to bulk availability
2026-01-24 multi seat work
2026-02-13 i2c helper
2026-02-13 clean up
2026-02-14 Optimize image assets and remove unreferenced images
2026-02-14 i2c for new devices modified
2026-02-14 Fix use-case guard, ignore KiCad locks
2026-02-17 Add G1 firmware build matrix workflow
2026-02-17 Publish G1 workflow via allowlist and ignore KiCad autosave files
2026-02-18 Remove Configuration section from README
2026-02-20 Revert "ci: add manual G2 C style workflow"
2026-02-20 slight change of page render
2026-03-07 AGENTS.md
2026-03-07 Release v0.14.1
2026-04-11 Release v0.16.0
2026-04-19 Release v0.17.0

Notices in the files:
hardware/circuit/README.md:
This hardware is published under the **CERN-OHL-S v2** license.
hardware/circuit/legacy/README.md:
This hardware is published under the **CERN-OHL-S v2** license. See `LICENSE.md` for details.
